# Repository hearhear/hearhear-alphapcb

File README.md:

hearhear-alphapcb
=================

PCBs for the alpha Hear Hear

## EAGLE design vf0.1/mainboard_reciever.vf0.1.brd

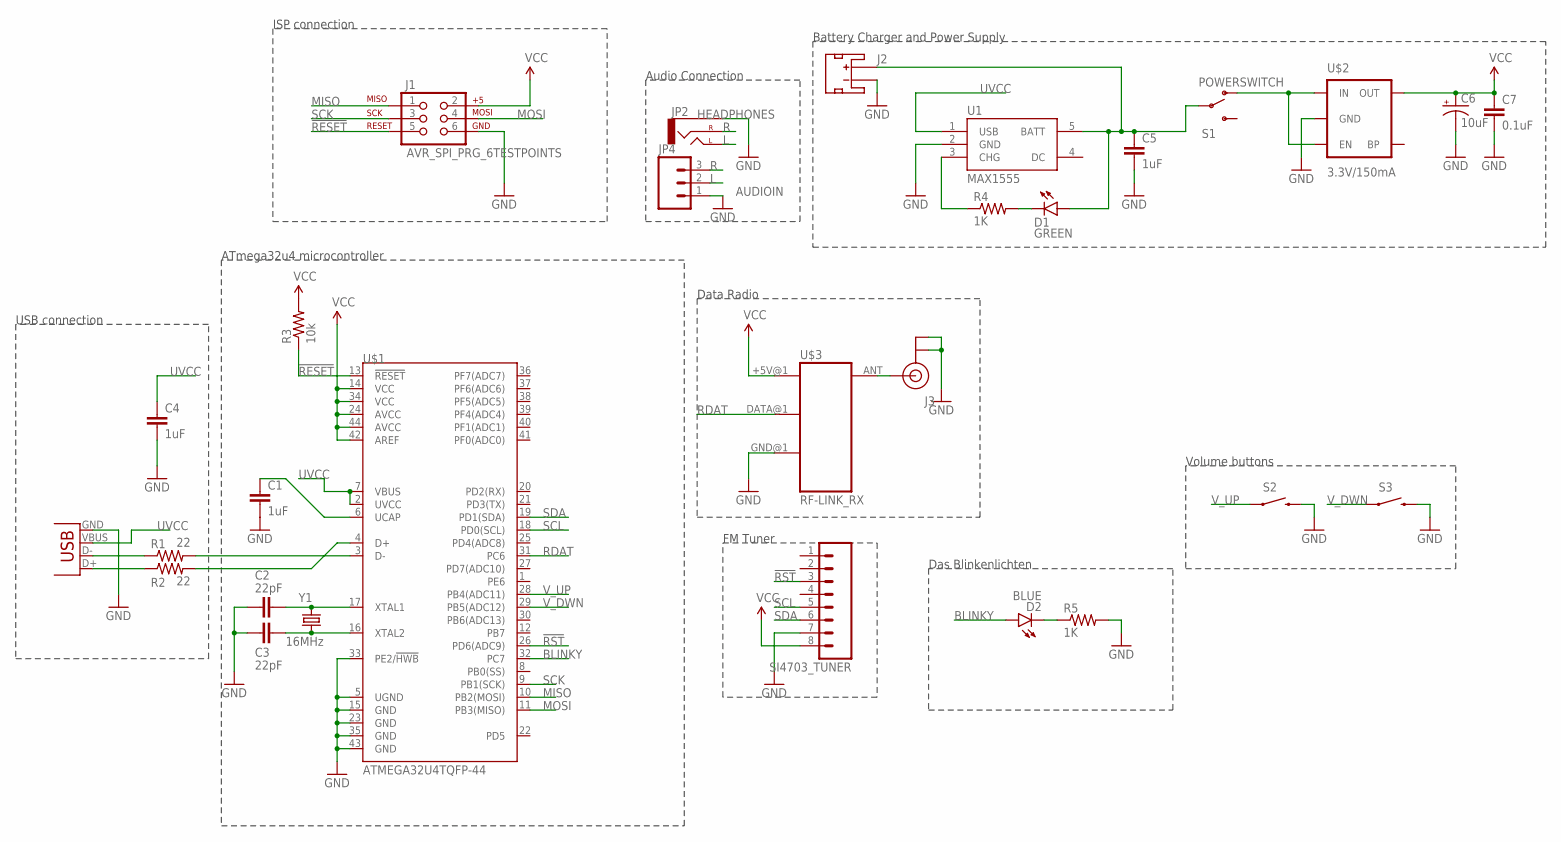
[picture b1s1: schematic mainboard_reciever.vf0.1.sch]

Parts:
C1, C4, C5: 1uF; 0603-CAP
C2, C3: 22pF; 0603-CAP
C6: 10uF; CPOL-RADIAL-10UF-25V
C7: 0.1uF; 0603-CAP
D1: GREEN; LED-0603
D2: BLUE; LED-0603
J1: AVR_SPI_PRG_6TESTPOINTS; 2X3_TEST_POINTS
J2: BATTERY; JST-2-SMD
J3: U.FL
JP1: USBSMD; USB-MINIB
JP2: HEADPHONES; AUDIO-JACK
JP4: AUDIOIN; 1X03
R1, R2: 22; 0603-RES
R3: 10k; 0603-RES
R4, R5: 1K; 0603-RES
S1: POWERSWITCH; SWITCH-SPDT-SMD
S2, S3: SWITCH-MOMENTARY-2SIDE_EZ; TACTILE-PTH-SIDEEZ
SI4703_TUNER: M08; 1X08_PIN1_NO_SILK
U1: MAX1555; SOT23-5
U$1: ATMEGA32U4TQFP-44; TQFP44
U$2: 3.3V/150mA; SOT23-5
U$3: RF-LINK_RX
Y1: 16MHz; CRYSTAL-SMD-5X3

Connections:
!RESET: J1.5, R3.1, U$1.13 (!RESET)
!RST: SI4703_TUNER.3, U$1.26 (PD6(ADC9))
BLINKY: D2.A, U$1.32 (PC7)
GND: C1.2, C2.1, C3.1, C4.2, C5.2, C6.2 (-), C7.2, J1.6, J2.1 (-), J3.P$1 (GND), J3.P$2 (GND), JP1.GND, JP2.SLEEVE, JP4.1, R5.2, S2.2, S3.2, SI4703_TUNER.7, U1.2 (GND), U$1.5 (UGND), U$1.15 (GND), U$1.23 (GND), U$1.33 (PE2/!HWB), U$1.35 (GND), U$1.43 (GND), U$2.2 (GND), U$3.GND@1 (GND)
L: JP2.TIP (LEFT), JP4.2
MISO: J1.1, U$1.10 (PB2(MOSI))
MOSI: J1.4, U$1.11 (PB3(MISO))
unnamed: JP1.D+, R2.1
unnamed: JP1.D-, R1.1
unnamed: R1.2, U$1.3 (D-)
unnamed: R2.2, U$1.4 (D+)
unnamed: C1.1, U$1.6 (UCAP)
unnamed: C2.2, U$1.17 (XTAL1), Y1.3 (2)
unnamed: C3.2, U$1.16 (XTAL2), Y1.1
unnamed: C5.1, D1.A, J2.2 (+), S1.2, U1.5 (BATT)
unnamed: D1.C, R4.2
unnamed: R4.1, U1.3 (CHG)
unnamed: S1.1 (O), U$2.1 (IN), U$2.3 (EN)
unnamed: J3.P$3 (SIGNAL), U$3.ANT
unnamed: D2.C, R5.1
R: JP2.RING (RIGHT), JP4.3
RDAT: U$1.31 (PC6), U$3.DATA@1 (DATA)
SCK: J1.3, U$1.9 (PB1(SCK))
SCL: SI4703_TUNER.5, U$1.18 (PD0(SCL))
SDA: SI4703_TUNER.6, U$1.19 (PD1(SDA))
UVCC: C4.1, JP1.VBUS, U1.1 (USB), U$1.2 (UVCC), U$1.7 (VBUS)
VCC: C6.1 (+), C7.1, J1.2, R3.2, SI4703_TUNER.8, U$1.14 (VCC), U$1.24 (AVCC), U$1.34 (VCC), U$1.42 (AREF), U$1.44 (AVCC), U$2.5 (OUT), U$3.+5V@1 (+5V)
V_DWN: S3.1, U$1.29 (PB5(ADC12))
V_UP: S2.1, U$1.28 (PB4(ADC11))

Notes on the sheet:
Audio Connection
ISP connection
ATmega32u4 microcontroller
USB connection
Battery Charger and Power Supply
Data Radio
FM Tuner
Das Blinkenlichten
Volume buttons

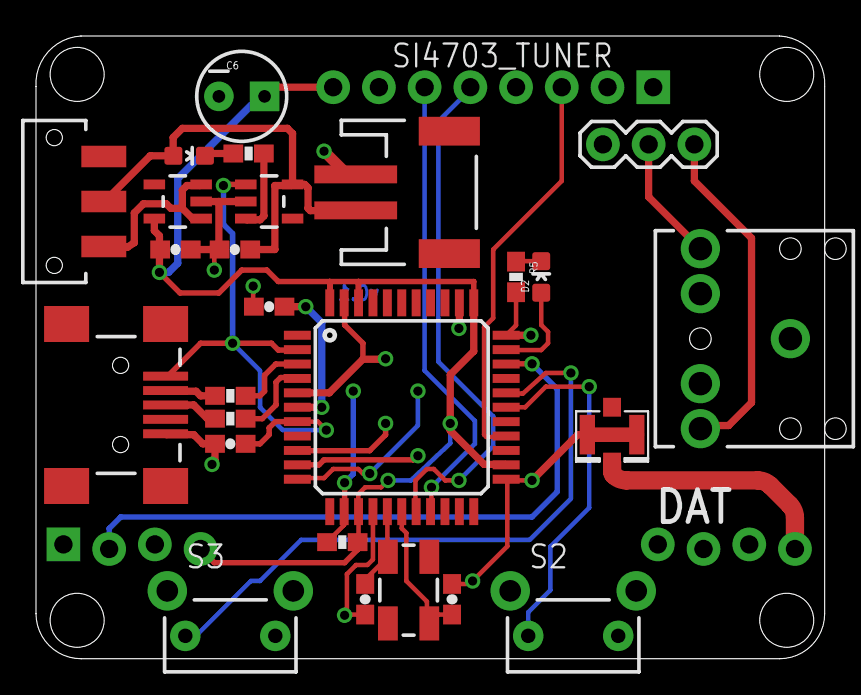
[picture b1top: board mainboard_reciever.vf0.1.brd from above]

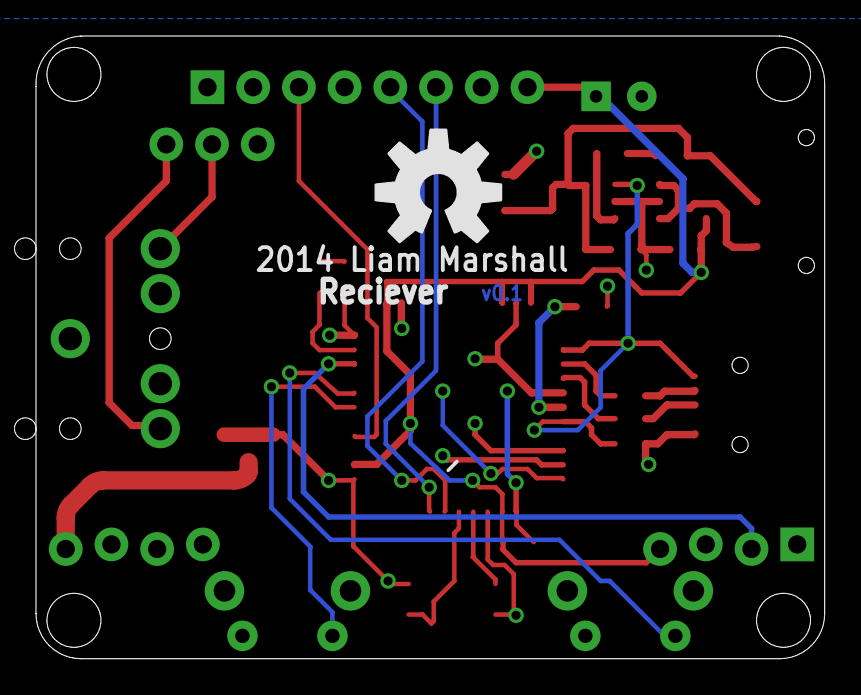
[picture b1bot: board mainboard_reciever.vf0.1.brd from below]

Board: 2 copper layers, 43.8 x 34.6 mm, 30 parts (2 on the bottom side), 29 nets.

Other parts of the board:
U$4: OSHW-LOGO-L

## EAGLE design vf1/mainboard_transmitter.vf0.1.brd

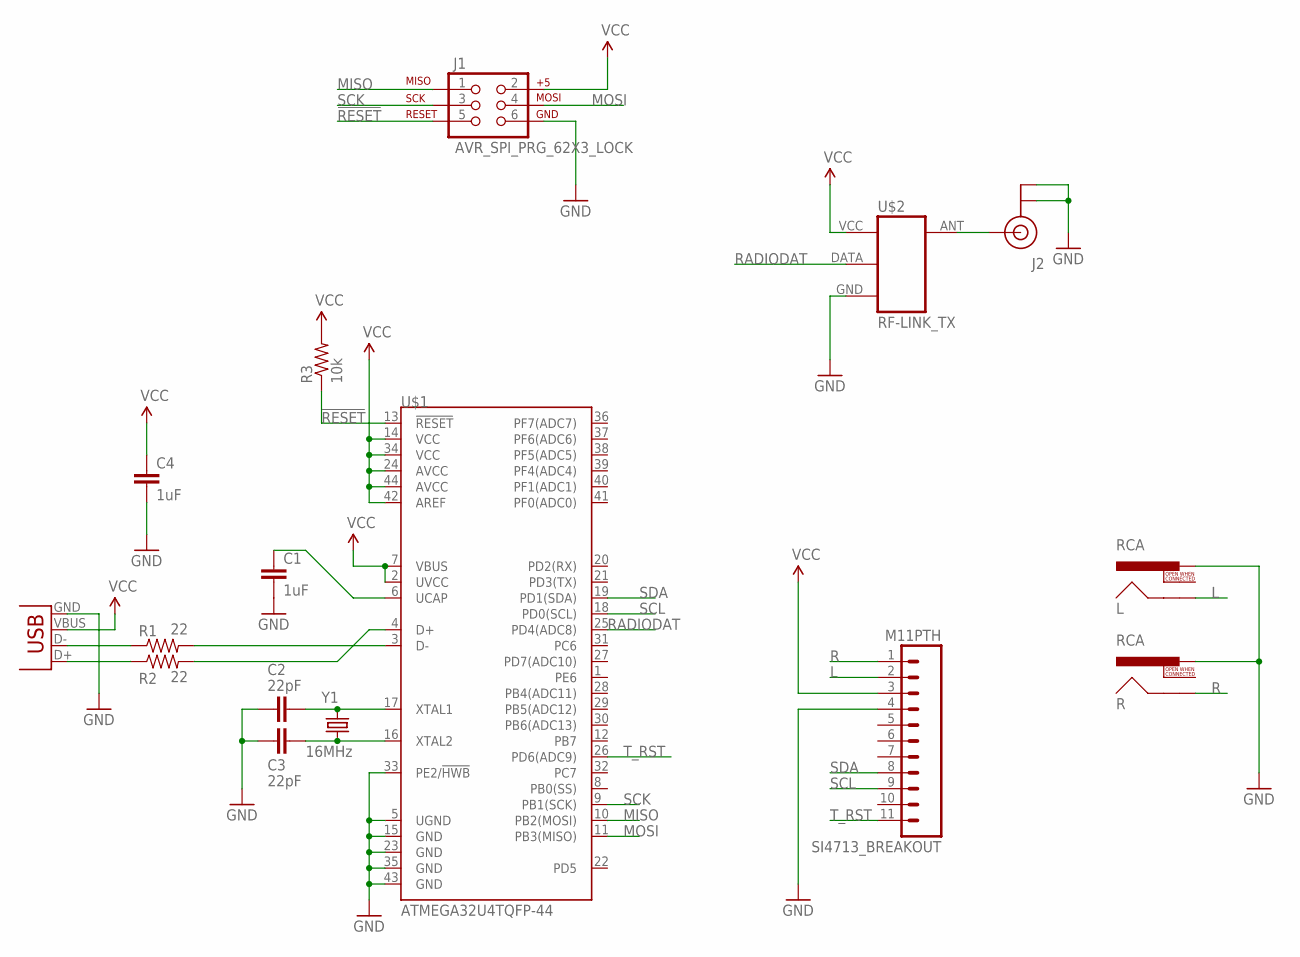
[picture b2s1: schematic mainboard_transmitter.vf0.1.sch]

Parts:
C1, C4: 1uF; CAP-PTH-SMALL
C2, C3: 22pF; CAP-PTH-SMALL
J1: AVR_SPI_PRG_62X3_LOCK; 2X3_LOCK
J2: U.FL
JP1: USB-B; USB-B-PTH
L: RCA
R: RCA
R1, R2: 22; AXIAL-0.1
R3: 10k; AXIAL-0.1
SI4713_BREAKOUT: M11PTH; 1X11
U$1: ATMEGA32U4TQFP-44; TQFP44
U$2: RF-LINK_TX
Y1: 16MHz; HC49US

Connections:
!RESET: J1.5, R3.P$1 (1), U$1.13 (!RESET)
GND: C1.2, C2.1, C3.1, C4.2, J1.6, J2.P$1 (GND), J2.P$2 (GND), JP1.GND, L.PIN, R.PIN, SI4713_BREAKOUT.4, U$1.5 (UGND), U$1.15 (GND), U$1.23 (GND), U$1.33 (PE2/!HWB), U$1.35 (GND), U$1.43 (GND), U$2.GND
L: L.SHELL, SI4713_BREAKOUT.2
MISO: J1.1, U$1.10 (PB2(MOSI))
MOSI: J1.4, U$1.11 (PB3(MISO))
unnamed: JP1.D+, R2.P$1 (1)
unnamed: JP1.D-, R1.P$1 (1)
unnamed: R1.P$2 (2), U$1.3 (D-)
unnamed: R2.P$2 (2), U$1.4 (D+)
unnamed: C1.1, U$1.6 (UCAP)
unnamed: C2.2, U$1.17 (XTAL1), Y1.2
unnamed: C3.2, U$1.16 (XTAL2), Y1.1
unnamed: J2.P$3 (SIGNAL), U$2.ANT
R: R.SHELL, SI4713_BREAKOUT.1
RADIODAT: U$1.25 (PD4(ADC8)), U$2.DATA
SCK: J1.3, U$1.9 (PB1(SCK))
SCL: SI4713_BREAKOUT.9, U$1.18 (PD0(SCL))
SDA: SI4713_BREAKOUT.8, U$1.19 (PD1(SDA))
T_RST: SI4713_BREAKOUT.11, U$1.26 (PD6(ADC9))
VCC: C4.1, J1.2, JP1.VBUS, R3.P$2 (2), SI4713_BREAKOUT.3, U$1.2 (UVCC), U$1.7 (VBUS), U$1.14 (VCC), U$1.24 (AVCC), U$1.34 (VCC), U$1.42 (AREF), U$1.44 (AVCC), U$2.VCC (+5V)

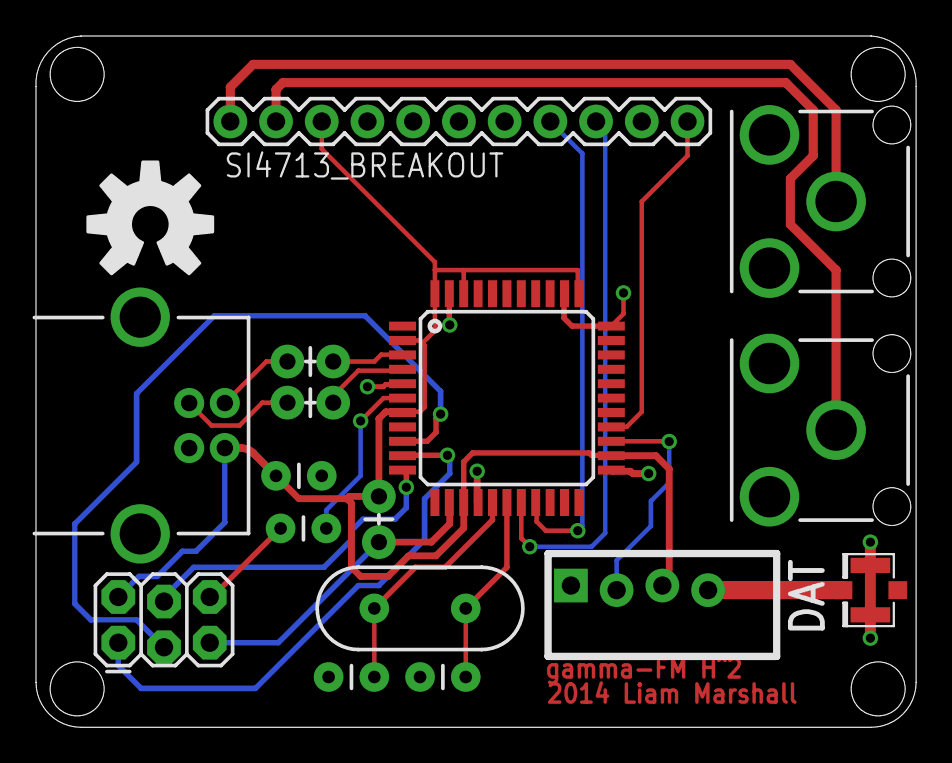
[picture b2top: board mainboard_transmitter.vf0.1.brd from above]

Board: 2 copper layers, 48.9 x 38.4 mm, 17 parts (0 on the bottom side), 20 nets.

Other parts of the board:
U$3: OSHW-LOGO-L

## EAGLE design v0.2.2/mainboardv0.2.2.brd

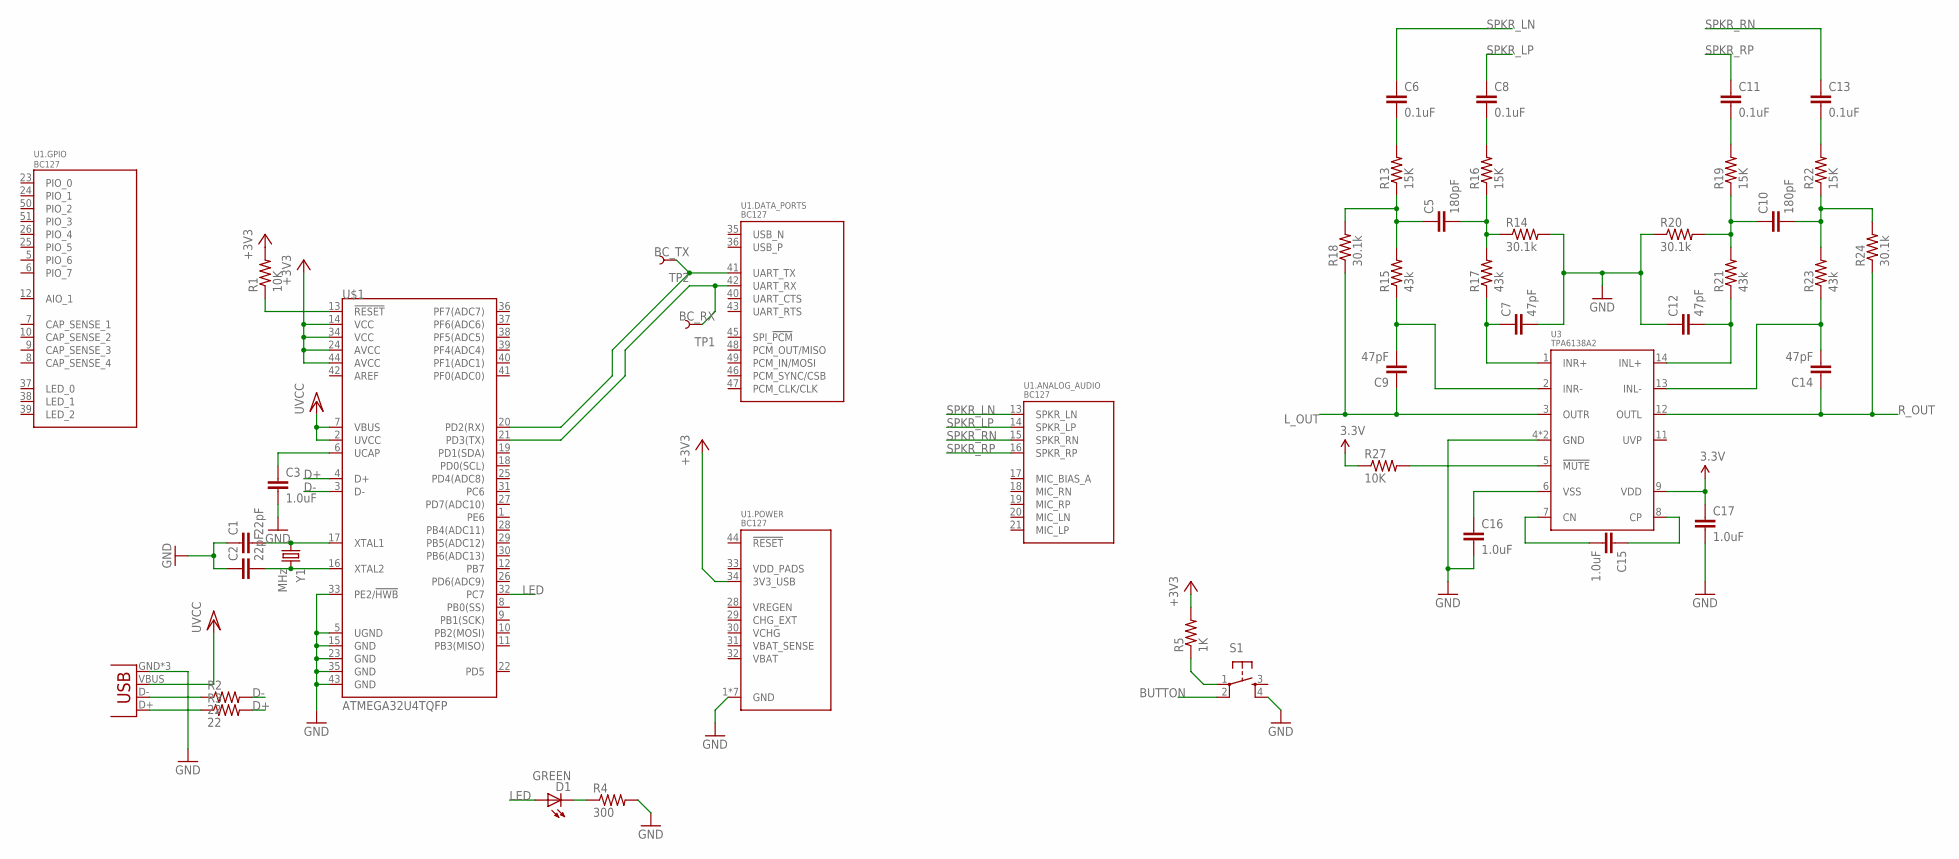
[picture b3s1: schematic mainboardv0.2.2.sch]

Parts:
C1, C2: 22pF; 0603-CAP
C3, C15, C16, C17: 1.0uF; 0603-CAP
C5, C10: 180pF; 0603-CAP
C6, C8, C11, C13: 0.1uF; 0603-CAP
C7, C9, C12, C14: 47pF; 0603-CAP
D1: GREEN; LED-1206
JP1: USB-MICROB
R1, R27: 10K; 0603-RES
R2, R3: 22; 0603-RES
R4: 300; 0603-RES
R5: 1K; 0603-RES
R13, R16, R19, R22: 15K; 0603-RES
R14, R18, R20, R24: 30.1k; 0603-RES
R15, R17, R21, R23: 43k; 0603-RES
S1: TAC_SWITCHSMD; TACTILE_SWITCH_SMD
TP1: BC_RX; PAD.02X.02
TP2: BC_TX; PAD.02X.02
U1: BC127
U3: TPA6138A2; TSSOP-14
U$1: ATMEGA32U4TQFP; SPARKFUN-DIGITALIC_TQFP44
Y1: MHz; CRYSTAL-SMD-5X3

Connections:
3.3V: C17.1, R27.1, U3.9 (VDD)
+3V3: R1.2, R5.2, U1.34 (3V3_USB), U$1.14 (VCC), U$1.24 (AVCC), U$1.34 (VCC), U$1.44 (AVCC)
BUTTON: S1.2
D+: R3.2, U$1.4 (D+)
D-: R2.2, U$1.3 (D-)
GND: C1.1, C2.1, C3.2, C7.2, C12.1, C16.2, C17.2, JP1.GND, JP1.MT1 (GND), JP1.MT2 (GND), R4.2, R14.2, R20.1, S1.4, U1.1 (GND), U1.2 (GND), U1.3 (GND), U1.4 (GND), U1.11 (GND), U1.22 (GND), U1.27 (GND), U3.4 (GND), U3.10 (GND), U$1.5 (UGND), U$1.15 (GND), U$1.23 (GND), U$1.33 (PE2/!HWB), U$1.35 (GND), U$1.43 (GND)
LED: D1.A, U$1.32 (PC7)
L_OUT: C9.1, R18.1, U3.3 (OUTR)
unnamed: R1.1, U$1.13 (!RESET)
unnamed: C1.2, U$1.17 (XTAL1), Y1.1
unnamed: C2.2, U$1.16 (XTAL2), Y1.3 (2)
unnamed: C3.1, U$1.6 (UCAP)
unnamed: D1.C, R4.1
unnamed: R5.1, S1.1
unnamed: JP1.D-, R2.1
unnamed: JP1.D+, R3.1
unnamed: TP2.P$1, U1.41 (UART_TX), U$1.20 (PD2(RX))
unnamed: TP1.P$1, U1.42 (UART_RX), U$1.21 (PD3(TX))
unnamed: C8.2, R16.2
unnamed: C6.2, R13.2
unnamed: C5.1, R13.1, R15.2, R18.2
unnamed: C9.2, R15.1, U3.2 (INR-)
unnamed: C7.1, R17.1, U3.1 (INR+)
unnamed: C5.2, R14.1, R16.1, R17.2
unnamed: C10.1, R19.1, R20.2, R21.2
unnamed: C12.2, R21.1, U3.14 (INL+)
unnamed: C11.2, R19.2
unnamed: C10.2, R22.1, R23.2, R24.2
unnamed: C13.2, R22.2
unnamed: C14.2, R23.1, U3.13 (INL-)
unnamed: R27.2, U3.5 (!MUTE)
unnamed: C16.1, U3.6 (VSS)
unnamed: C15.2, U3.7 (CN)
unnamed: C15.1, U3.8 (CP)
R_OUT: C14.1, R24.1, U3.12 (OUTL)
SPKR_LN: C6.1, U1.13 (SPKR_LN)
SPKR_LP: C8.1, U1.14 (SPKR_LP)
SPKR_RN: C13.1, U1.15 (SPKR_RN)
SPKR_RP: C11.1, U1.16 (SPKR_RP)
VCC/2: JP1.VBUS, U$1.2 (UVCC), U$1.7 (VBUS)

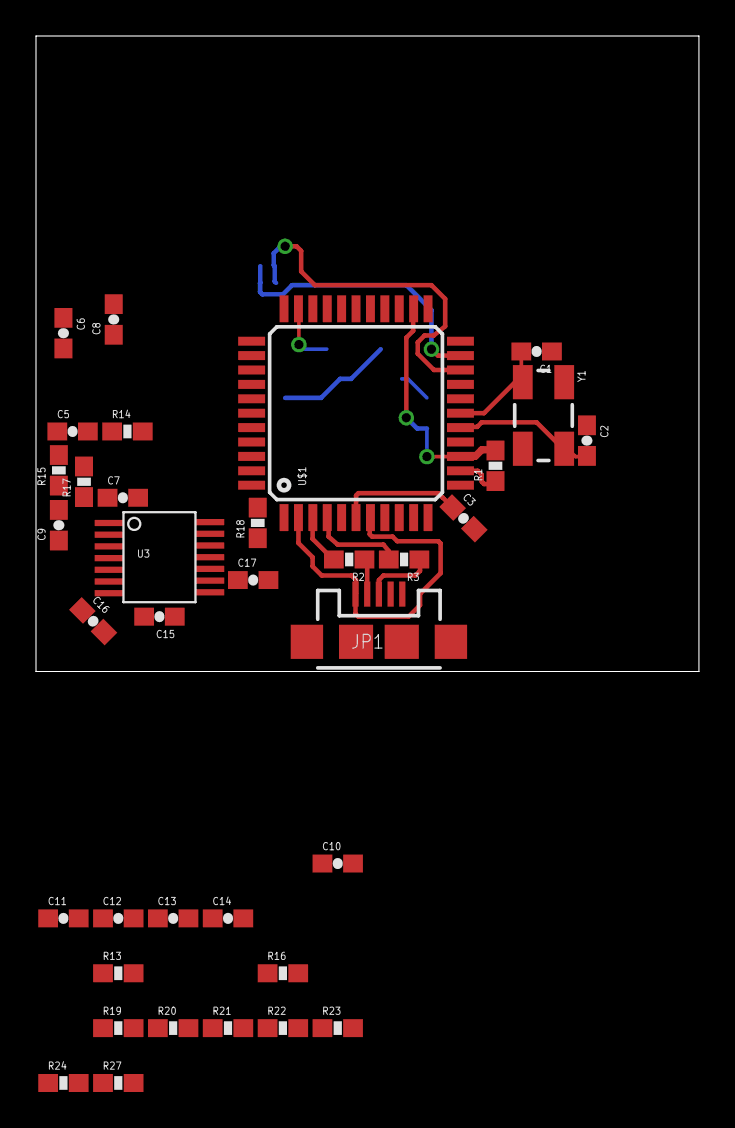
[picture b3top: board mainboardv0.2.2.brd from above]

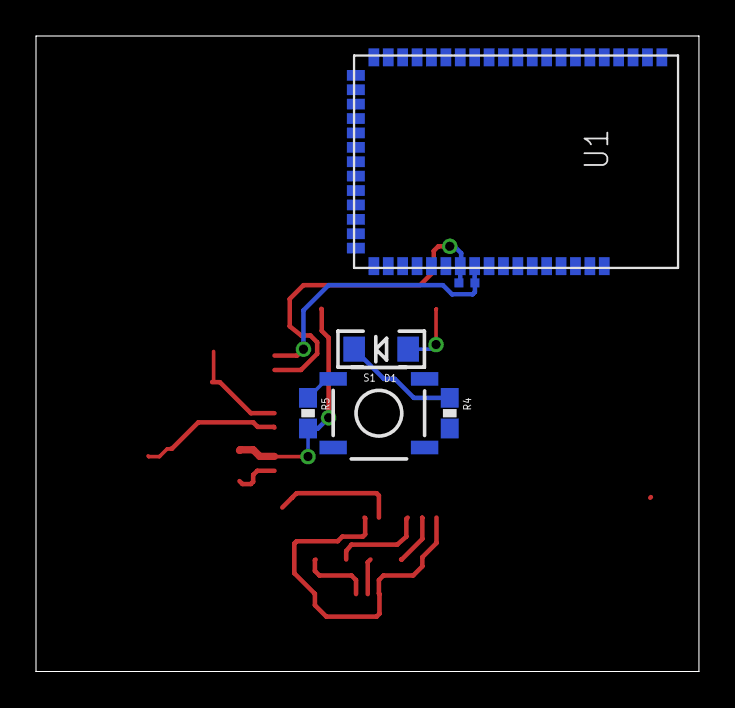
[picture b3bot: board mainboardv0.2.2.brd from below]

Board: 2 copper layers, 36.8 x 35.3 mm, 43 parts (7 on the bottom side), 39 nets.

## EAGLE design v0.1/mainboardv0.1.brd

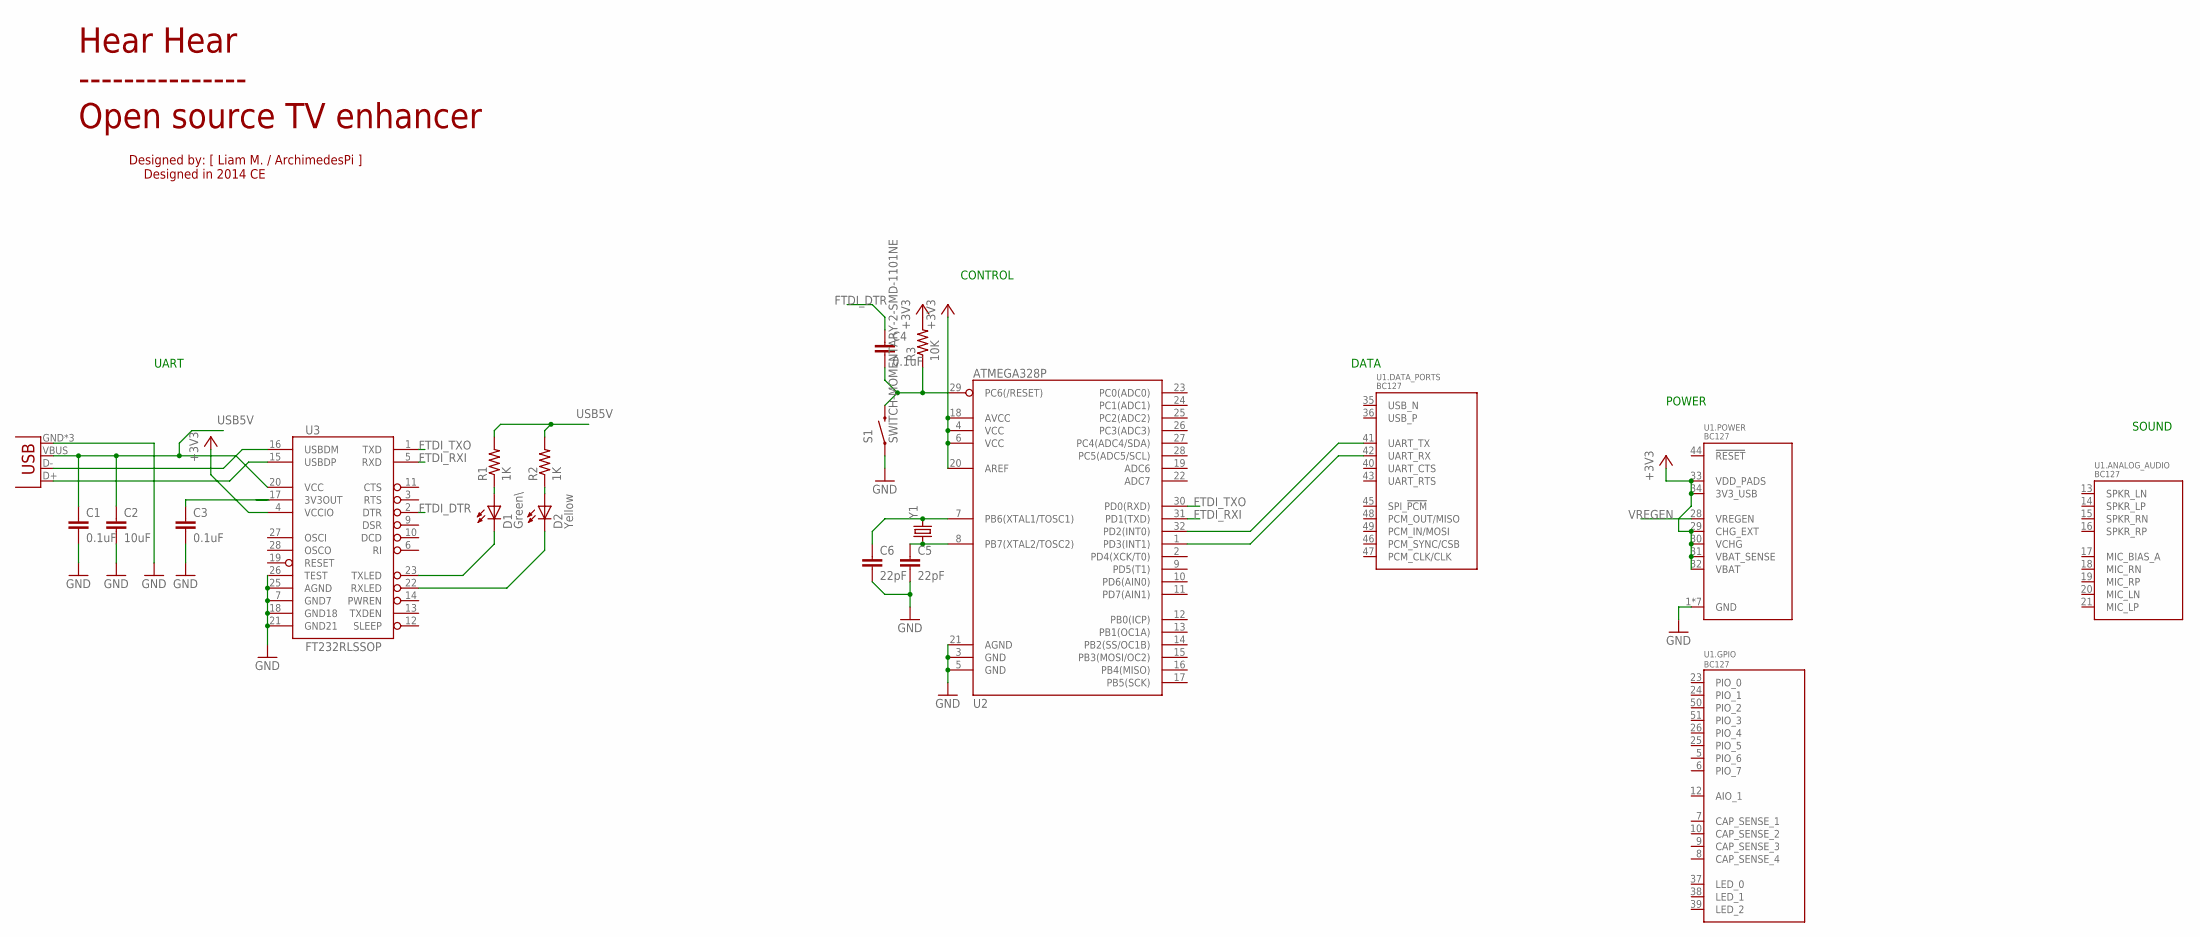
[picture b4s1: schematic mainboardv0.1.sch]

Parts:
C1, C3, C4: 0.1uF; 0603-CAP
C2: 10uF; 0603-CAP
C5, C6: 22pF; 0603-CAP
D1: Green\; LED-0603
D2: Yellow; LED-0603
JP1: USB-MICROB
R1, R2: 1K; 0603-RES
R3: 10K; 0603-RES
S1: SWITCH-MOMENTARY-2-SMD-1101NE; TACTILE-SWITCH-1101NE
U1: BC127
U2: ATMEGA328P; TQFP32-08
U3: FT232RLSSOP; SSOP28DB
Y1: CRYSTALHC49US; HC49US

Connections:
+3V3: R3.2, U1.29 (CHG_EXT), U1.30 (VCHG), U1.31 (VBAT_SENSE), U1.32 (VBAT), U1.33 (VDD_PADS), U1.34 (3V3_USB), U2.4 (VCC), U2.6 (VCC), U2.18 (AVCC), U2.20 (AREF), U3.4 (VCCIO)
BC127_UART_RXI: U1.42 (UART_RX), U2.1 (PD3(INT1))
BC127_UART_TXO: U1.41 (UART_TX), U2.32 (PD2(INT0))
FTDI_DTR: C4.1, U3.2 (DTR)
FTDI_RXI: U2.31 (PD1(TXD)), U3.5 (RXD)
FTDI_TXO: U2.30 (PD0(RXD)), U3.1 (TXD)
GND: C1.2, C2.2, C3.2, C5.2, C6.2, JP1.GND, JP1.MT1 (GND), JP1.MT2 (GND), S1.P$1 (1), U1.1 (GND), U1.2 (GND), U1.3 (GND), U1.4 (GND), U1.11 (GND), U1.22 (GND), U1.27 (GND), U2.3 (GND), U2.5 (GND), U2.21 (AGND), U3.7 (GND7), U3.18 (GND18), U3.21 (GND21), U3.25 (AGND), U3.26 (TEST)
unnamed: JP1.D-, U3.16 (USBDM)
unnamed: JP1.D+, U3.15 (USBDP)
unnamed: C4.2, R3.1, S1.P$2 (2), U2.29 (PC6(/RESET))
unnamed: C3.1, U3.17 (3V3OUT)
unnamed: D1.A, R1.1
unnamed: D2.A, R2.1
unnamed: D1.C, U3.23 (TXLED)
unnamed: D2.C, U3.22 (RXLED)
unnamed: C6.1, U2.7 (PB6(XTAL1/TOSC1)), Y1.2
unnamed: C5.1, U2.8 (PB7(XTAL2/TOSC2)), Y1.1
USB5V: C1.1, C2.1, JP1.VBUS, R1.2, R2.2, U3.20 (VCC)
VREGEN: U1.28 (VREGEN)

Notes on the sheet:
POWER
SOUND
DATA
CONTROL
UART
Designed by: [ Liam M. / ArchimedesPi ] Designed in 2014 CE
Hear Hear --------------- Open source TV enhancer

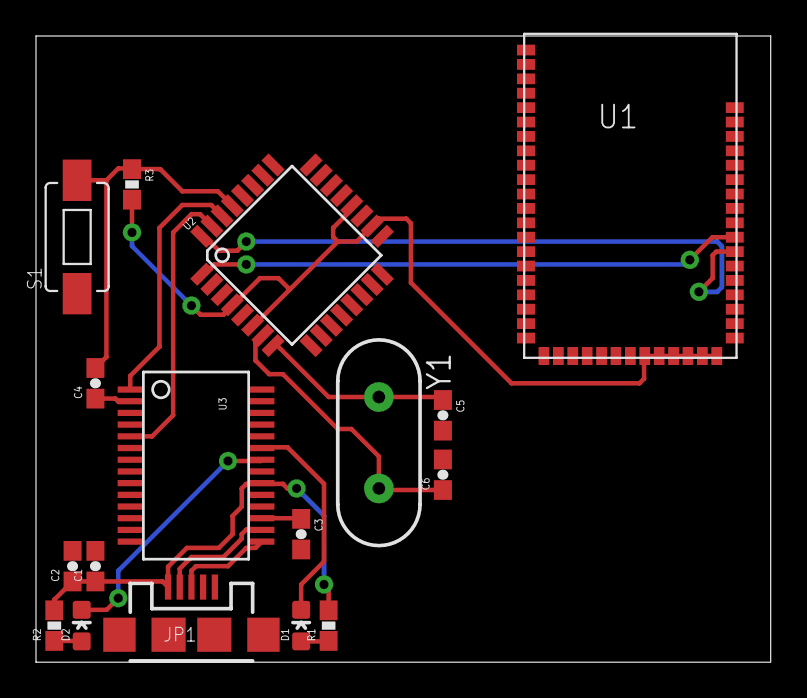
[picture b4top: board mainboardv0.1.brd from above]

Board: 2 copper layers, 40.8 x 34.8 mm, 17 parts (0 on the bottom side), 18 nets.

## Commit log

2014-08-09 Add version 0.1
2014-08-09 Add v0.2
2014-08-09 add files
2014-08-16 Copy over for new version
2014-08-16 Begin the routing
2014-08-16 Routed the button and LED
2014-08-16 More routing
2014-08-17 Add gitter badge
2014-10-21 New FM-based γ prototype for Grandpa
2014-10-21 Mostly complete, routed audio, FM transmitter, data transmitter
2014-10-23 Ignore gerbers
2014-10-23 Final revision of vf0.1
2014-10-23 Finalized transmitter main board
2014-10-29 Add everything
2014-11-19 Finalized. Yep, it got sent to fab and came back!
2014-11-19 Reciever stuff. Not done yet :)
2014-11-19 vf1 - Moves ISP header.
2014-11-30 Add some silk and copper identifiers
2014-11-30 Tweak labelling a bit
2015-02-26 Remove that (bad) version

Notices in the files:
parts and their libraries:
SparkFun-RF: Licensing: Creative Commons ShareAlike 4.0 International - https://creativecommons.org/licenses/by-sa/4.0
SparkFun-AnalogIC: Licensing: CC v3.0 Share-Alike You are welcome to use this library for commercial purposes.
